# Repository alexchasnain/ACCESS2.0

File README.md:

# ACCESS2.0
Automated Cartridge-based Cancer Early Screening System and its accompanying software supporting instrumentation for magnetofluidics automating sample-to-answer cancer methylation biomarker detection

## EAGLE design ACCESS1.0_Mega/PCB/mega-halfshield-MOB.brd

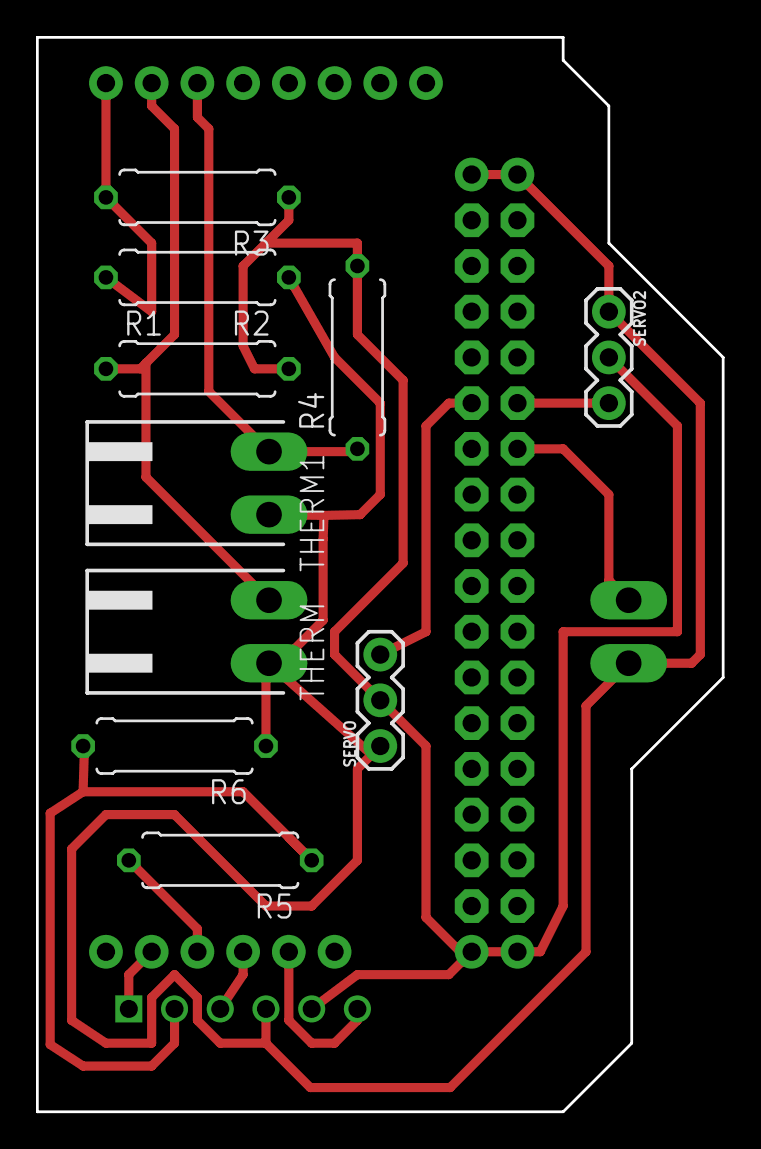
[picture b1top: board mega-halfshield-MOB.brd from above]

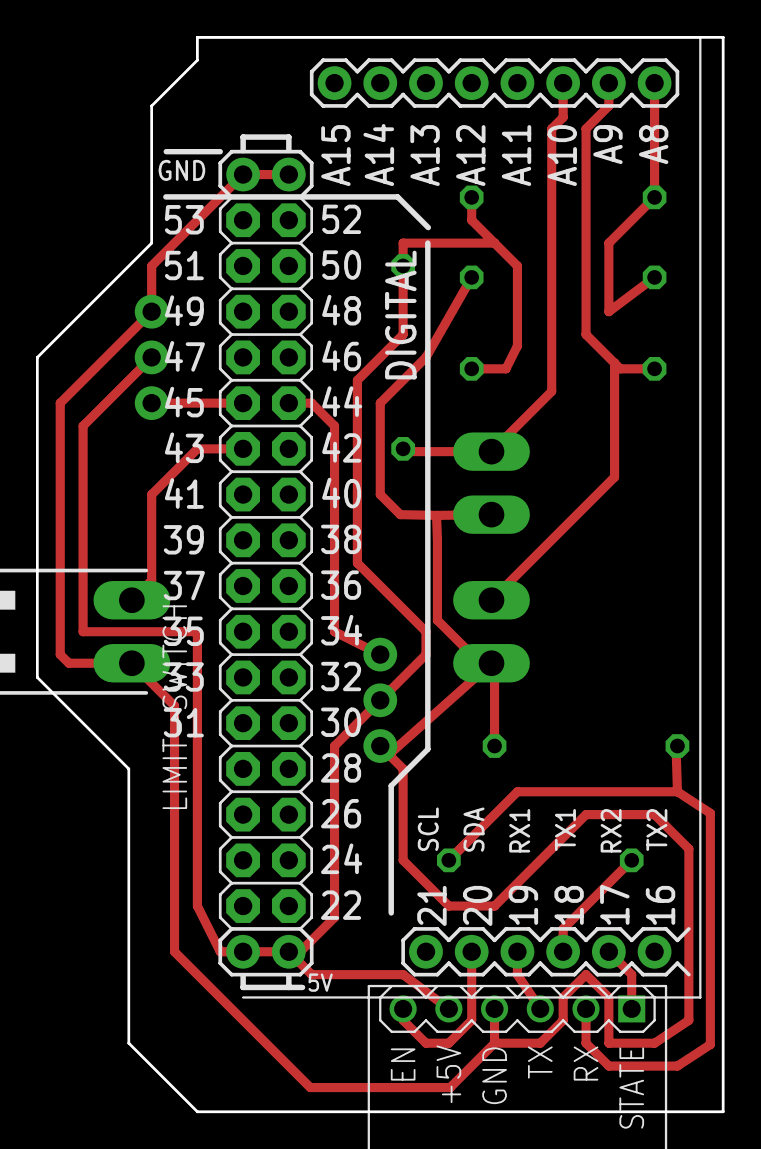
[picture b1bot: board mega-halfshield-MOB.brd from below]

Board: 2 copper layers, 38.1 x 59.7 mm, 13 parts (3 on the bottom side), 13 nets.

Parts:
LIMIT-SWITCH: 90-2
R1, R2, R3, R4, R5, R6: 0309/10
SERVO: Mag-Servo; 1X03
SERVO2: Fluo-Servo; 1X03
THERM: BC-therm; 90-2
THERM1: PCR-therm; 90-2
U$1: ARDUINO_MEGA_R3_HALFSHIELD; ARDUINO_MEGA_HALFSHIELD
U$2: WIRELESS-BLUETOOTH-HC-05

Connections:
+5V: R1.2, R3.1, R4.2, SERVO.2, SERVO2.2, U$1.5V@1, U$1.5V@2, U$2.5
A8: R2.2, R3.2, U$1.A8
A9: R1.1, THERM.1, U$1.A9
A10: R4.1, THERM1.1, U$1.A10
GND: LIMIT-SWITCH.2, R2.1, R6.1, SERVO.1, SERVO2.1, THERM.2, THERM1.2, U$1.GND@2, U$1.GND@3, U$2.4
unnamed: LIMIT-SWITCH.1, U$1.43
unnamed: R5.1, R6.2, U$2.2
P17: U$1.17, U$2.1
P18-TX1: R5.2, U$1.18
P19-RX1: U$1.19, U$2.3
P20: U$1.20, U$2.6
P44: SERVO.3, U$1.44
P45: SERVO2.3, U$1.45

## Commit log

2021-11-05 POC MOB 2.0 initial upload
2021-11-10 Updated MOB2.0_Mega and reorganized files
    MOB2.0_Mega/heater.cpp and MOB2.0_Mega/heater.h are fully updated. MOB2.0_Mega/motors.cpp, MOB2.0_Mega/motors.h, MOB2.0_Mega/serialcomm.cpp, and MOB2.0_Mega/serialcomm.h are partially updated. Also r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
2021-11-17 Still updating Arduino code but started updating Python code too
    Mostly made changes in motors.cpp/motors.h and started updating temp.py too
2021-11-17 Previously uploaded wrong MOB analysis script
2022-12-12 Heating Update
    Comms between Pi and Mega to leave time for imaging
2023-05-02 File reorganization and renaming
2023-05-02 File reorganization

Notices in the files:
parts and their libraries:
SparkFun-Connectors: Licensing: Creative Commons ShareAlike 4.0 International - https://creativecommons.org/licenses/by-sa/4.0
diy-modules: Released under the Creative Commons Attribution 4.0 International License: http://creativecommons.org/licenses/by/4.0
